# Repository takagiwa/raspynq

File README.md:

# raspynq
Xilinx Virtual Cable Server adapter for Raspberry Pi

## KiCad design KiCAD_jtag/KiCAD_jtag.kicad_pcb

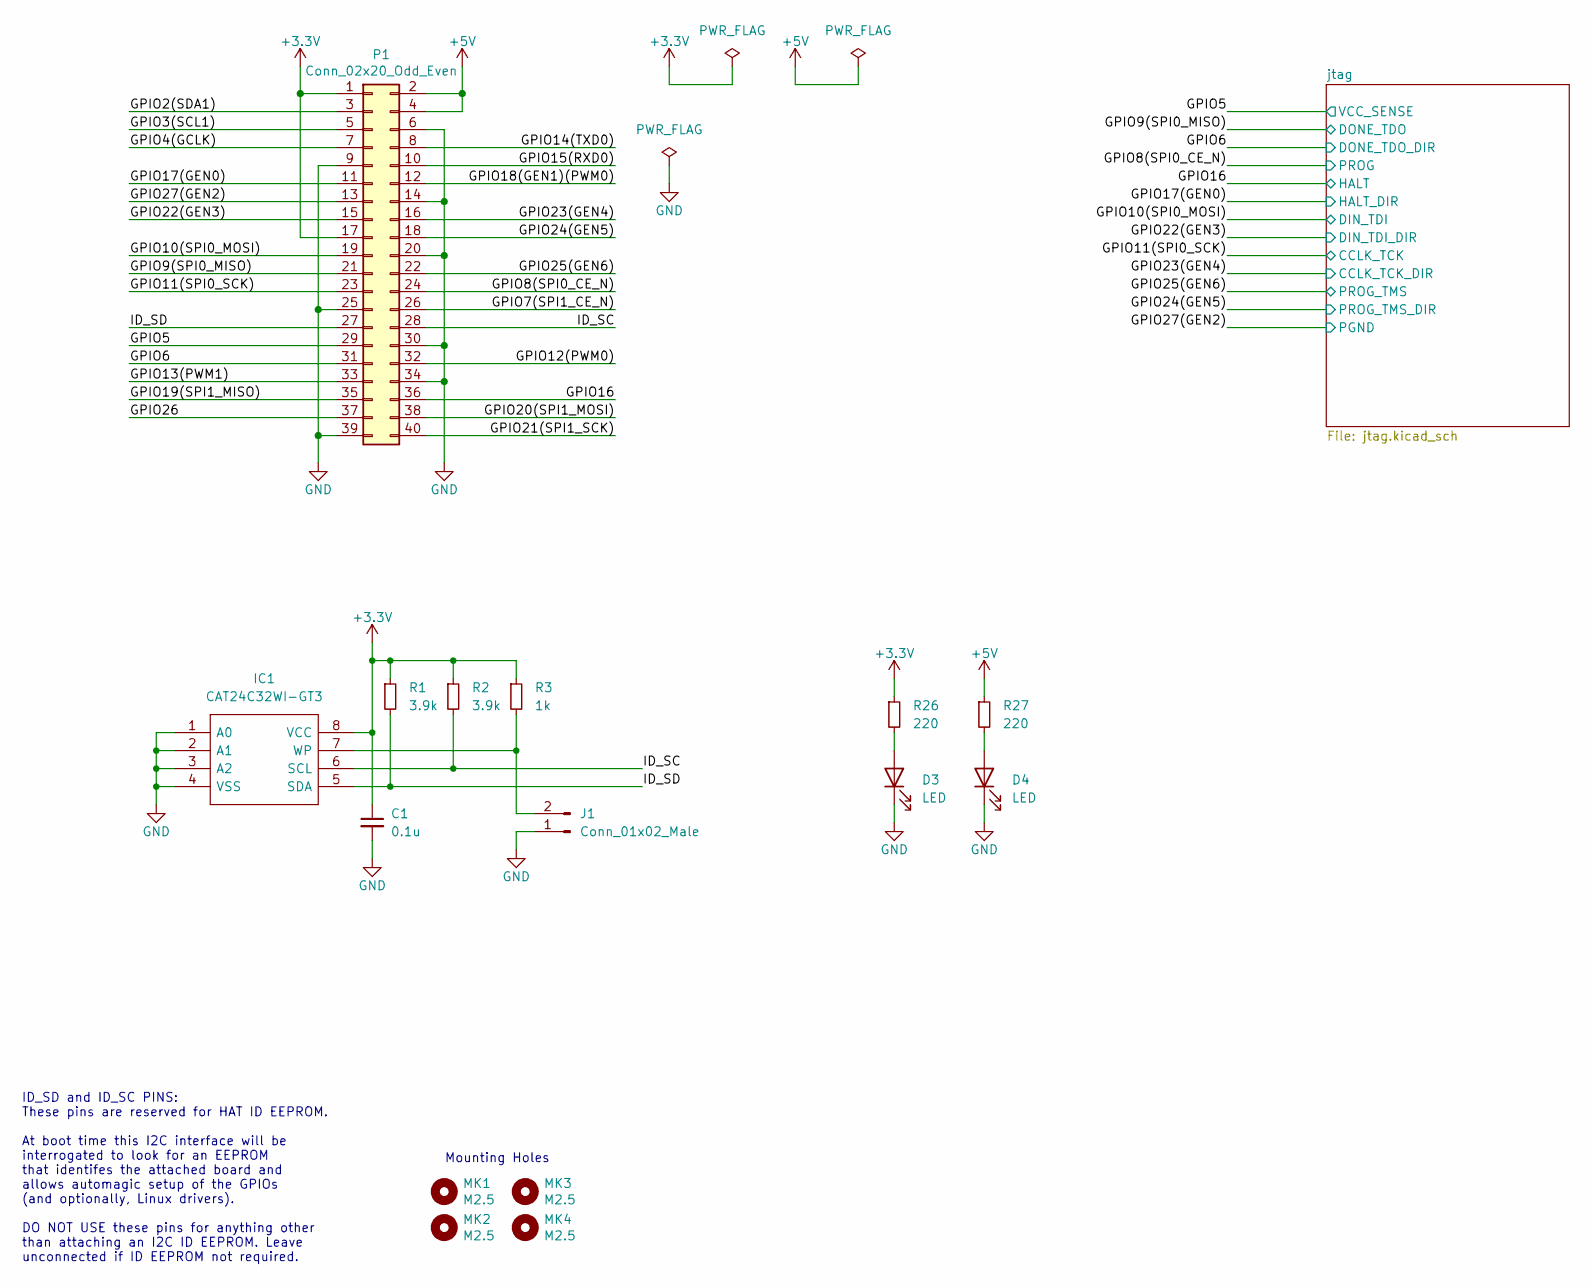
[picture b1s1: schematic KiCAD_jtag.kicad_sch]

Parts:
C1: 0.1u; C_0805_2012Metric_Pad1.18x1.45mm_HandSolder
D3, D4: LED; LED_0805_2012Metric_Pad1.15x1.40mm_HandSolder
IC1: CAT24C32WI-GT3; SOIC127P600X175-8N; Mouser Part Number 698-CAT24C32WI-GT3
J1: Conn_01x02_Male; PinHeader_1x02_P2.54mm_Vertical
MK1, MK2, MK3, MK4: M2.5; MountingHole_2.7mm_M2.5
P1: Conn_02x20_Odd_Even; PinSocket_2x20_P2.54mm_Vertical
R1, R2: 3.9k; R_0805_2012Metric_Pad1.20x1.40mm_HandSolder
R3: 1k; R_0805_2012Metric_Pad1.20x1.40mm_HandSolder
R26, R27: 220; R_0805_2012Metric_Pad1.20x1.40mm_HandSolder

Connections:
+3V3: C1.1, IC1.8 (VCC), P1.1, P1.17, R1.1, R2.1, R3.1, R26.1; also elsewhere on the board
+5V: P1.2, P1.4, R27.1
/GPIO2(SDA1): P1.3
/GPIO3(SCL1): P1.5
/GPIO4(GCLK): P1.7
/GPIO5: P1.29; also elsewhere on the board
/GPIO6: P1.31; also elsewhere on the board
/GPIO7(SPI1_CE_N): P1.26
/GPIO8(SPI0_CE_N): P1.24; also elsewhere on the board
/GPIO9(SPI0_MISO): P1.21; also elsewhere on the board
/GPIO10(SPI0_MOSI): P1.19; also elsewhere on the board
/GPIO11(SPI0_SCK): P1.23; also elsewhere on the board
/GPIO12(PWM0): P1.32
/GPIO13(PWM1): P1.33
/GPIO14(TXD0): P1.8
/GPIO15(RXD0): P1.10
/GPIO16: P1.36; also elsewhere on the board
/GPIO17(GEN0): P1.11; also elsewhere on the board
/GPIO18(GEN1)(PWM0): P1.12
/GPIO19(SPI1_MISO): P1.35
/GPIO20(SPI1_MOSI): P1.38
/GPIO21(SPI1_SCK): P1.40
/GPIO22(GEN3): P1.15; also elsewhere on the board
/GPIO23(GEN4): P1.16; also elsewhere on the board
/GPIO24(GEN5): P1.18; also elsewhere on the board
/GPIO25(GEN6): P1.22; also elsewhere on the board
/GPIO26: P1.37
/GPIO27(GEN2): P1.13; also elsewhere on the board
/ID_SC: IC1.6 (SCL), P1.28, R2.2
/ID_SD: IC1.5 (SDA), P1.27, R1.2
GND: C1.2, D3.1 (K), D4.1 (K), IC1.1 (A0), IC1.2 (A1), IC1.3 (A2), IC1.4 (VSS), J1.1, P1.6, P1.9, P1.14, P1.20, P1.25, P1.30, P1.34, P1.39; also elsewhere on the board
unnamed: D3.2 (A), R26.2
unnamed: D4.2 (A), R27.2
unnamed: IC1.7 (WP), J1.2, R3.2

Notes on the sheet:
ID_SD and ID_SC PINS: These pins are reserved for HAT ID EEPROM. At boot time this I2C interface will be interrogated to look for an EEPROM that identifes the attached board and allows automagic setup of the GPIOs (and optionally, Linux drivers). DO NOT USE these pins for anything other than attach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
Mounting Holes

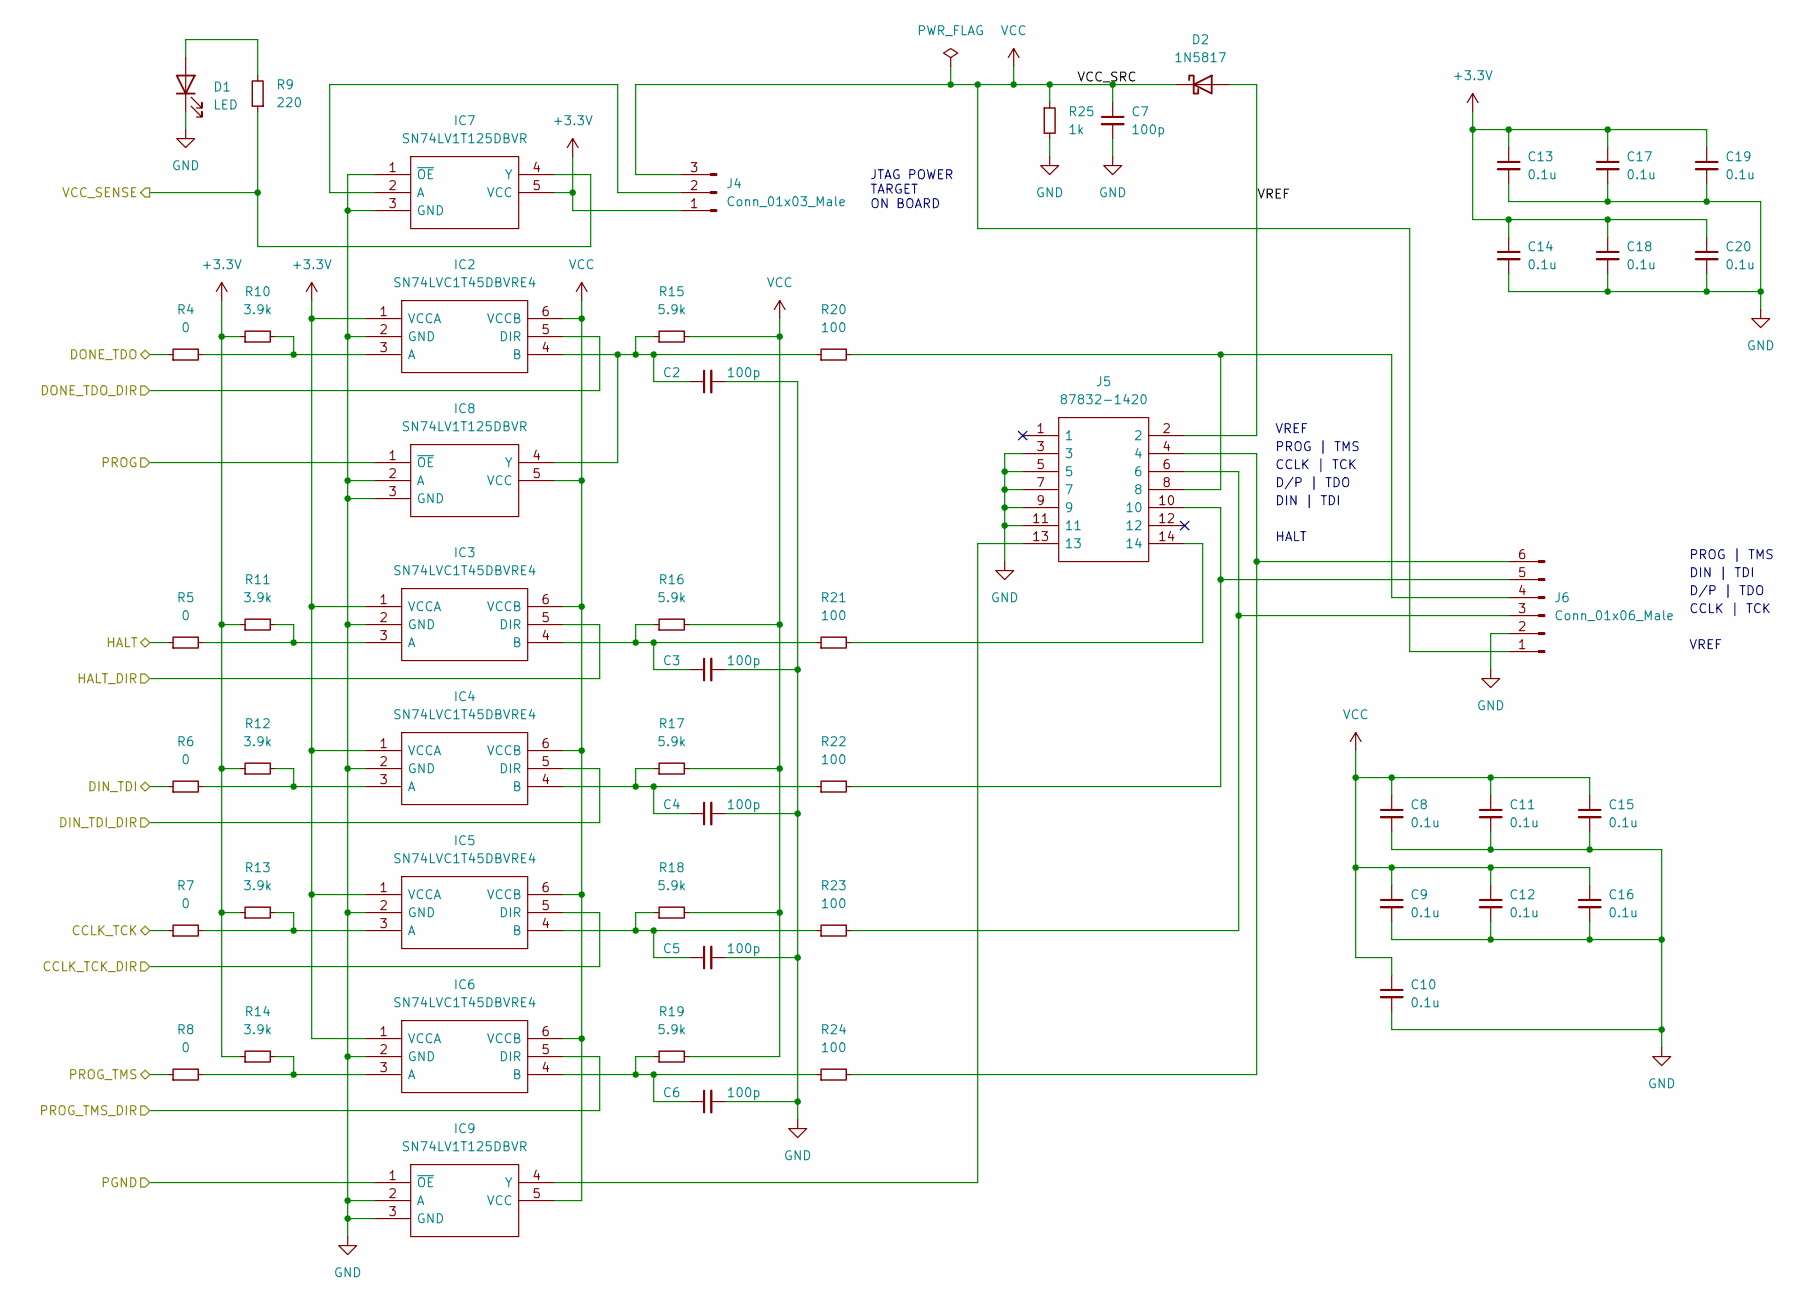
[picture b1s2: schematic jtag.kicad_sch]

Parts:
C2, C3, C4, C5, C6, C7: 100p; C_0805_2012Metric_Pad1.18x1.45mm_HandSolder
C8, C9, C10, C11, C12, C13, C14, C15, C16, C17, C18, C19, C20: 0.1u; C_0805_2012Metric_Pad1.18x1.45mm_HandSolder
D1: LED; LED_0805_2012Metric_Pad1.15x1.40mm_HandSolder
D2: 1N5817; D_DO-41_SOD81_P10.16mm_Horizontal
IC2, IC3, IC4, IC5, IC6: SN74LVC1T45DBVRE4; SOT95P280X145-6N; Mouser Part Number 595-74LVC1T45DBVRE4
IC7, IC8, IC9: SN74LV1T125DBVR; SOT95P280X145-5N; Mouser Part Number 595-SN74LV1T125DBVR
J4: Conn_01x03_Male; PinHeader_1x03_P2.54mm_Vertical
J5: 87832-1420; Mouser Part Number 538-87832-1420
J6: Conn_01x06_Male; PinHeader_1x06_P2.54mm_Vertical
R4, R5, R6, R7, R8: 0; R_0805_2012Metric_Pad1.20x1.40mm_HandSolder
R9: 220; R_0805_2012Metric_Pad1.20x1.40mm_HandSolder
R10, R11, R12, R13, R14: 3.9k; R_0805_2012Metric_Pad1.20x1.40mm_HandSolder
R15, R16, R17, R18, R19: 5.9k; R_0805_2012Metric_Pad1.20x1.40mm_HandSolder
R20, R21, R22, R23, R24: 100; R_0805_2012Metric_Pad1.20x1.40mm_HandSolder
R25: 1k; R_0805_2012Metric_Pad1.20x1.40mm_HandSolder

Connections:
+3V3: C13.1, C14.1, C17.1, C18.1, C19.1, C20.1, IC2.1 (VCCA), IC3.1 (VCCA), IC4.1 (VCCA), IC5.1 (VCCA), IC6.1 (VCCA), IC7.5 (VCC), J4.1, R10.1, R11.1, R12.1, R13.1, R14.1; also elsewhere on the board
/GPIO5: IC7.4 (Y), R9.1; also elsewhere on the board
/GPIO6: IC2.5 (DIR); also elsewhere on the board
/GPIO8(SPI0_CE_N): IC8.1 (~OE); also elsewhere on the board
/GPIO9(SPI0_MISO): R4.1; also elsewhere on the board
/GPIO10(SPI0_MOSI): R6.1; also elsewhere on the board
/GPIO11(SPI0_SCK): R7.1; also elsewhere on the board
/GPIO16: R5.1; also elsewhere on the board
/GPIO17(GEN0): IC3.5 (DIR); also elsewhere on the board
/GPIO22(GEN3): IC4.5 (DIR); also elsewhere on the board
/GPIO23(GEN4): IC5.5 (DIR); also elsewhere on the board
/GPIO24(GEN5): IC6.5 (DIR); also elsewhere on the board
/GPIO25(GEN6): R8.1; also elsewhere on the board
/GPIO27(GEN2): IC9.1 (~OE); also elsewhere on the board
/jtag/VREF: D2.2 (A), J5.2
GND: C2.2, C3.2, C4.2, C5.2, C6.2, C7.2, C8.2, C9.2, C10.2, C11.2, C12.2, C13.2, C14.2, C15.2, C16.2, C17.2, C18.2, C19.2, C20.2, D1.1 (K), IC2.2 (GND), IC3.2 (GND), IC4.2 (GND), IC5.2 (GND), IC6.2 (GND), IC7.1 (~OE), IC7.3 (GND), IC8.2 (A), IC8.3 (GND), IC9.2 (A), IC9.3 (GND), J5.3, J5.5, J5.7, J5.9, J5.11, J6.2, R25.2; also elsewhere on the board
unnamed: C2.1, IC2.4 (B), IC8.4 (Y), R15.1, R20.1
unnamed: C3.1, IC3.4 (B), R16.1, R21.1
unnamed: C4.1, IC4.4 (B), R17.1, R22.1
unnamed: C5.1, IC5.4 (B), R18.1, R23.1
unnamed: C6.1, IC6.4 (B), R19.1, R24.1
unnamed: D1.2 (A), R9.2
unnamed: IC2.3 (A), R4.2, R10.2
unnamed: IC3.3 (A), R5.2, R11.2
unnamed: IC4.3 (A), R6.2, R12.2
unnamed: IC5.3 (A), R7.2, R13.2
unnamed: IC6.3 (A), R8.2, R14.2
unnamed: IC7.2 (A), J4.2
unnamed: IC9.4 (Y), J5.13
unnamed: J5.4, J6.6, R24.2
unnamed: J5.6, J6.3, R23.2
unnamed: J5.8, J6.4, R20.2
unnamed: J5.10, J6.5, R22.2
unnamed: J5.14, R21.2
VCC: C7.1, C8.1, C9.1, C10.1, C11.1, C12.1, C15.1, C16.1, D2.1 (K), IC2.6 (VCCB), IC3.6 (VCCB), IC4.6 (VCCB), IC5.6 (VCCB), IC6.6 (VCCB), IC8.5 (VCC), IC9.5 (VCC), J4.3, J6.1, R15.2, R16.2, R17.2, R18.2, R19.2, R25.1

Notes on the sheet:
CCLK | TCK
VREF
PROG | TMS
D/P | TDO
HALT
DIN | TDI
JTAG POWER TARGET ON BOARD

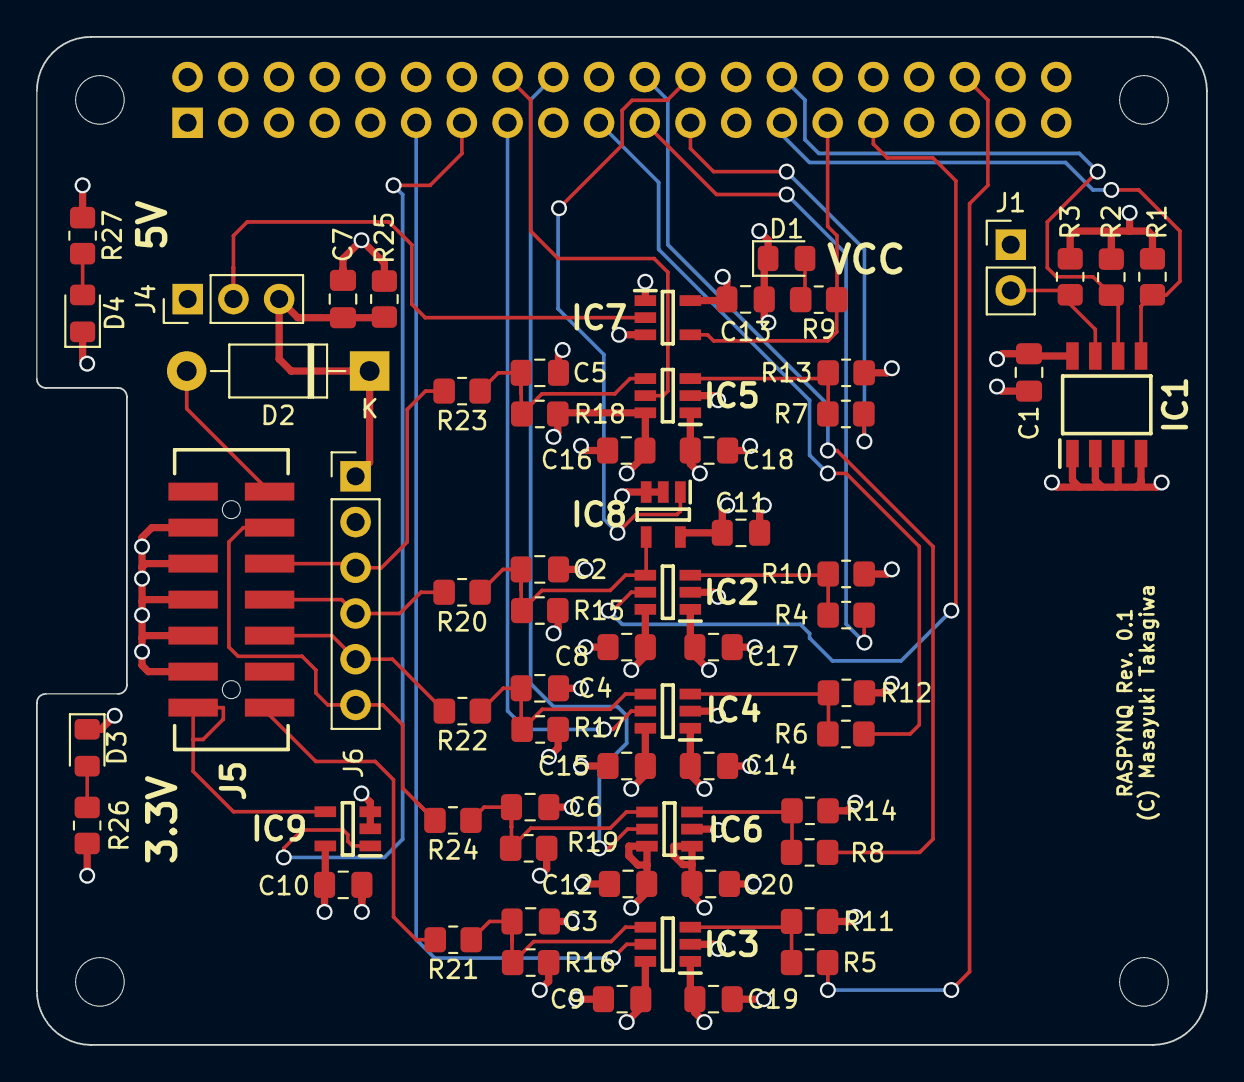
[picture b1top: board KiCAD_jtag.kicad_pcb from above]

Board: 4 copper layers, 65.0 x 56.0 mm, 69 parts (1 on the bottom side), 41 nets.

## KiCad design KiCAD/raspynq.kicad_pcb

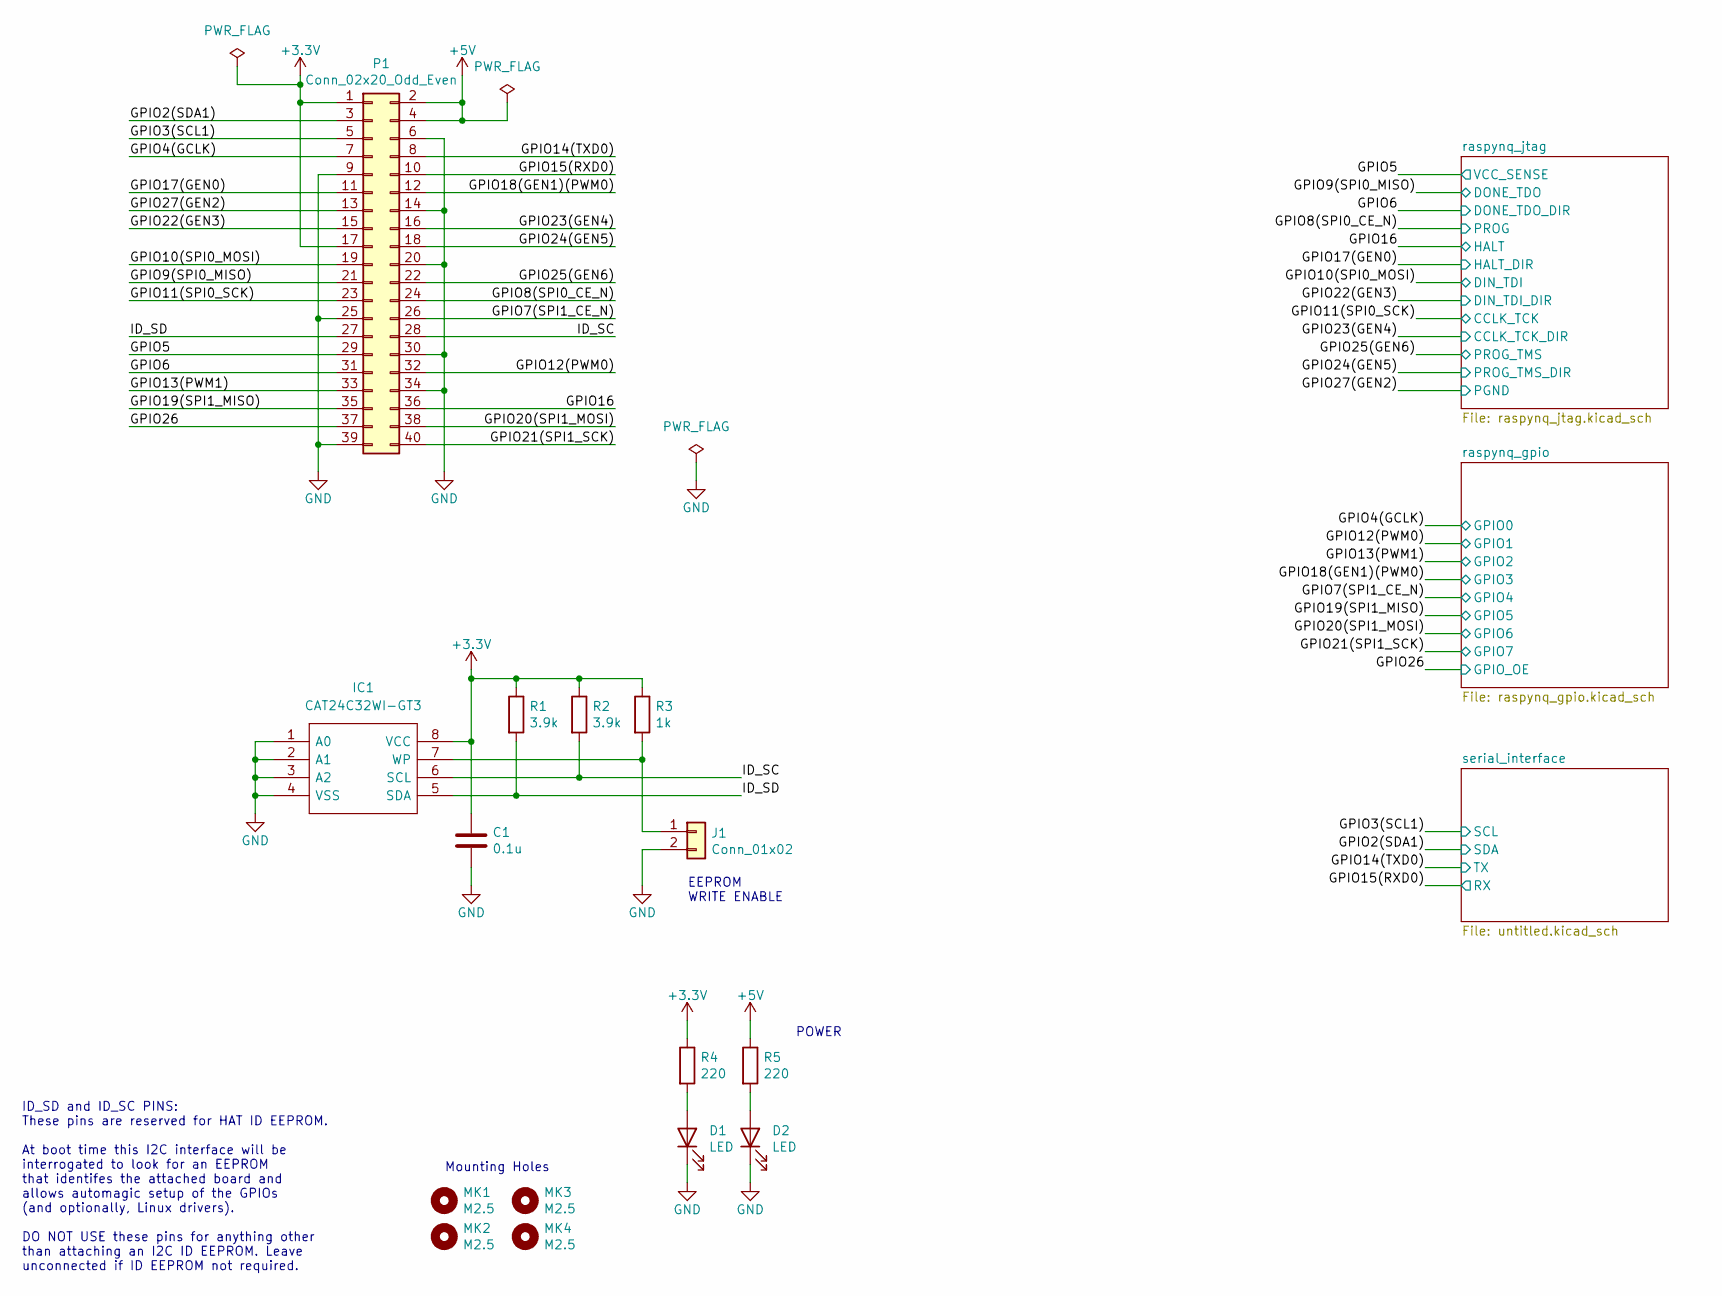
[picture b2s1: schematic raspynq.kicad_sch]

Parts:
C1: 0.1u; C_0805_2012Metric_Pad1.18x1.45mm_HandSolder
D1, D2: LED; LED_0805_2012Metric_Pad1.15x1.40mm_HandSolder
IC1: CAT24C32WI-GT3; SOIC127P600X175-8N; Mouser Part Number 698-CAT24C32WI-GT3
J1: Conn_01x02; PinHeader_1x02_P2.54mm_Vertical
MK1, MK2, MK3, MK4: M2.5; MountingHole_2.7mm_M2.5
P1: Conn_02x20_Odd_Even; PinSocket_2x20_P2.54mm_Vertical
R1, R2: 3.9k; R_0805_2012Metric_Pad1.20x1.40mm_HandSolder
R3: 1k; R_0805_2012Metric_Pad1.20x1.40mm_HandSolder
R4, R5: 220; R_0805_2012Metric_Pad1.20x1.40mm_HandSolder

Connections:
+3V3: C1.1, IC1.8 (VCC), P1.1, P1.17, R1.1, R2.1, R3.1, R4.1; also elsewhere on the board
+5V: P1.2, P1.4, R5.1; also elsewhere on the board
/GPIO2(SDA1): P1.3; also elsewhere on the board
/GPIO3(SCL1): P1.5; also elsewhere on the board
/GPIO4(GCLK): P1.7; also elsewhere on the board
/GPIO5: P1.29; also elsewhere on the board
/GPIO6: P1.31; also elsewhere on the board
/GPIO7(SPI1_CE_N): P1.26; also elsewhere on the board
/GPIO8(SPI0_CE_N): P1.24; also elsewhere on the board
/GPIO9(SPI0_MISO): P1.21; also elsewhere on the board
/GPIO10(SPI0_MOSI): P1.19; also elsewhere on the board
/GPIO11(SPI0_SCK): P1.23; also elsewhere on the board
/GPIO12(PWM0): P1.32; also elsewhere on the board
/GPIO13(PWM1): P1.33; also elsewhere on the board
/GPIO14(TXD0): P1.8; also elsewhere on the board
/GPIO15(RXD0): P1.10; also elsewhere on the board
/GPIO16: P1.36; also elsewhere on the board
/GPIO17(GEN0): P1.11; also elsewhere on the board
/GPIO18(GEN1)(PWM0): P1.12; also elsewhere on the board
/GPIO19(SPI1_MISO): P1.35; also elsewhere on the board
/GPIO20(SPI1_MOSI): P1.38; also elsewhere on the board
/GPIO21(SPI1_SCK): P1.40; also elsewhere on the board
/GPIO22(GEN3): P1.15; also elsewhere on the board
/GPIO23(GEN4): P1.16; also elsewhere on the board
/GPIO24(GEN5): P1.18; also elsewhere on the board
/GPIO25(GEN6): P1.22; also elsewhere on the board
/GPIO26: P1.37; also elsewhere on the board
/GPIO27(GEN2): P1.13; also elsewhere on the board
/ID_SC: IC1.6 (SCL), P1.28, R2.2
/ID_SD: IC1.5 (SDA), P1.27, R1.2
GND: C1.2, D1.1 (K), D2.1 (K), IC1.1 (A0), IC1.2 (A1), IC1.3 (A2), IC1.4 (VSS), J1.2, P1.6, P1.9, P1.14, P1.20, P1.25, P1.30, P1.34, P1.39; also elsewhere on the board
unnamed: D1.2 (A), R4.2
unnamed: D2.2 (A), R5.2
unnamed: IC1.7 (WP), J1.1, R3.2

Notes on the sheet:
Mounting Holes
EEPROM WRITE ENABLE
ID_SD and ID_SC PINS: These pins are reserved for HAT ID EEPROM. At boot time this I2C interface will be interrogated to look for an EEPROM that identifes the attached board and allows automagic setup of the GPIOs (and optionally, Linux drivers). DO NOT USE these pins for anything other than attach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
POWER

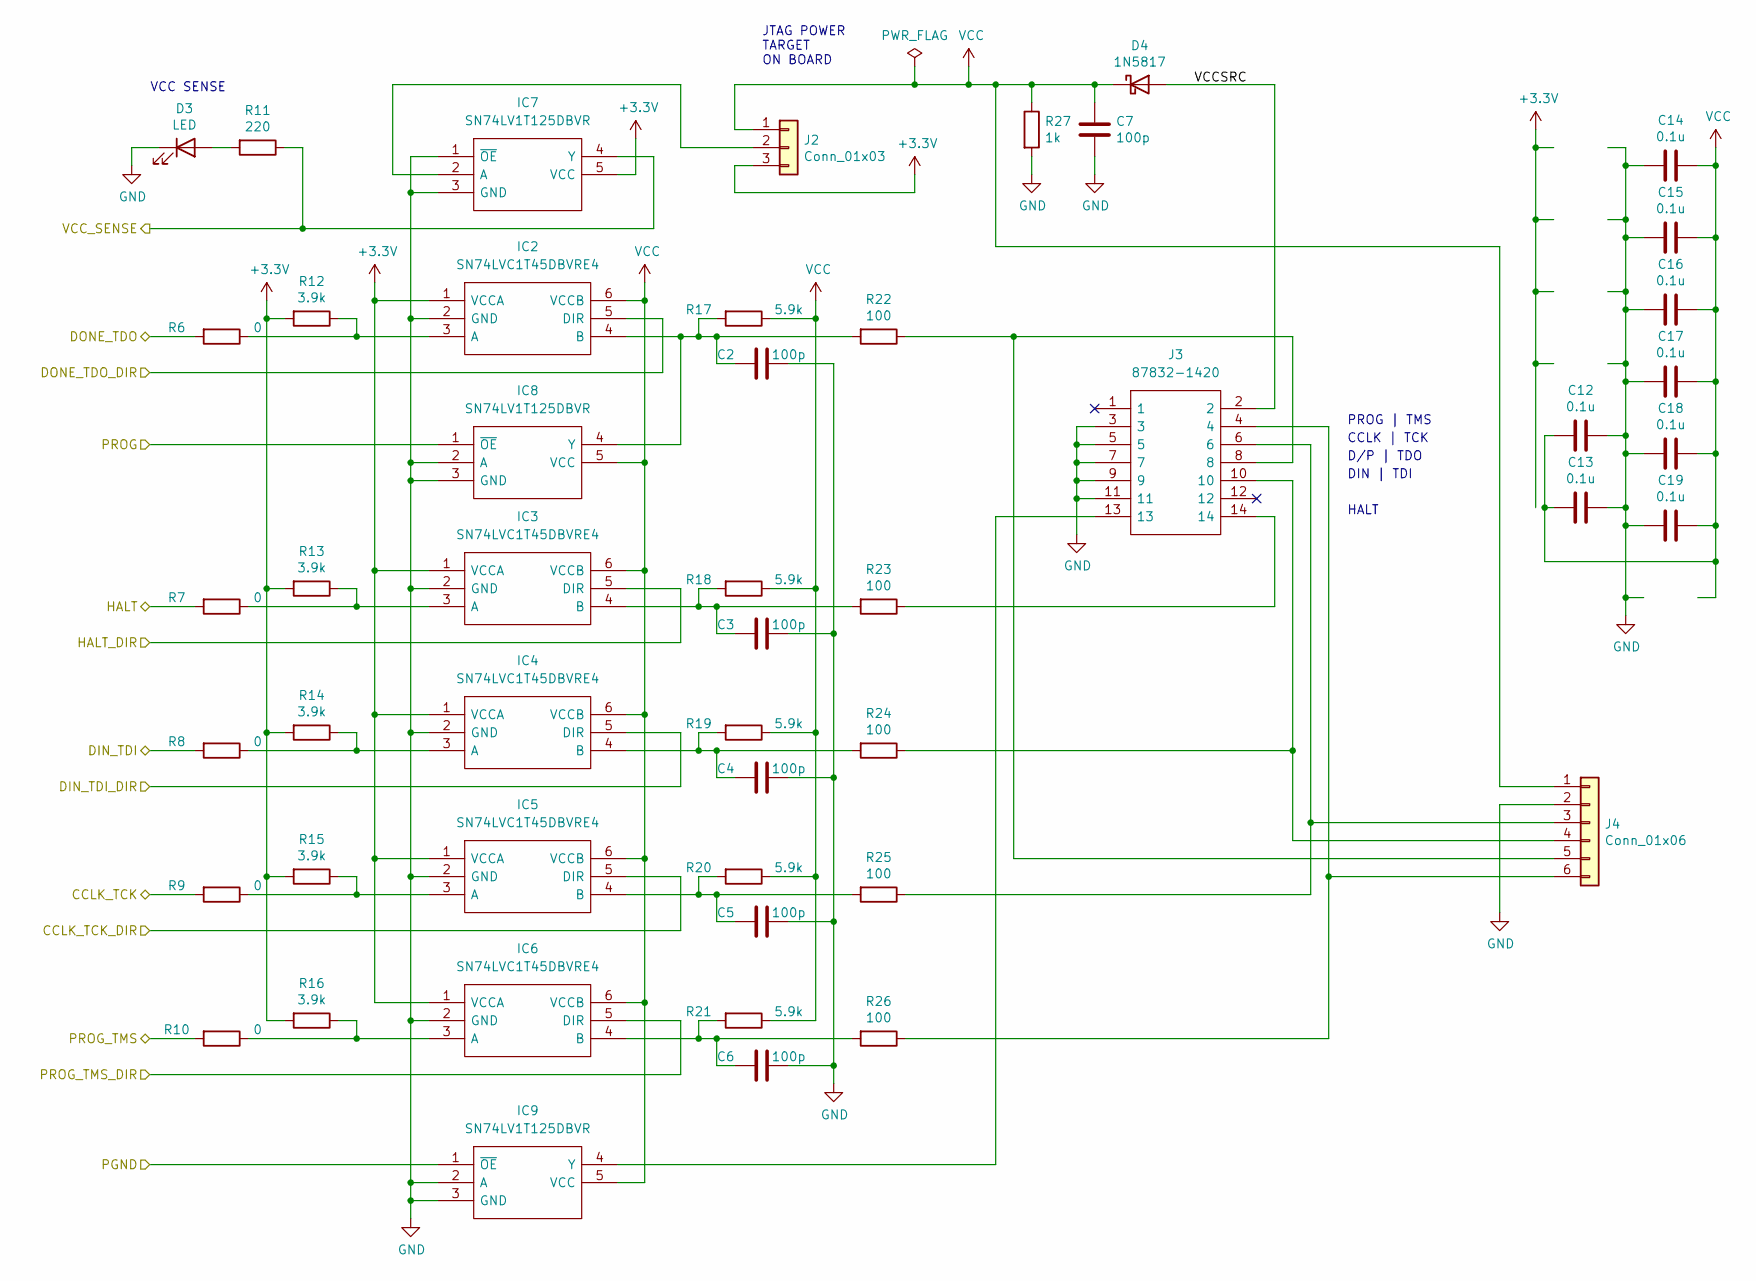
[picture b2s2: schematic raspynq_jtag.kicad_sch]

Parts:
C2, C3, C4, C5, C6, C7: 100p; C_0805_2012Metric_Pad1.18x1.45mm_HandSolder
C12, C13, C14, C15, C16, C17, C18, C19: 0.1u; C_0805_2012Metric_Pad1.18x1.45mm_HandSolder
D3: LED; LED_0805_2012Metric_Pad1.15x1.40mm_HandSolder
D4: 1N5817; D_DO-41_SOD81_P10.16mm_Horizontal
IC2, IC3, IC4, IC5, IC6: SN74LVC1T45DBVRE4; SOT95P280X145-6N; Mouser Part Number 595-74LVC1T45DBVRE4
IC7, IC8, IC9: SN74LV1T125DBVR; SOT95P280X145-5N; Mouser Part Number 595-SN74LV1T125DBVR
J2: Conn_01x03; PinHeader_1x03_P2.54mm_Vertical
J3: 87832-1420; Mouser Part Number 538-87832-1420
J4: Conn_01x06; PinHeader_1x06_P2.54mm_Vertical
R6, R7, R8, R9, R10: 0; R_0805_2012Metric_Pad1.20x1.40mm_HandSolder
R11: 220; R_0805_2012Metric_Pad1.20x1.40mm_HandSolder
R12, R13, R14, R15, R16: 3.9k; R_0805_2012Metric_Pad1.20x1.40mm_HandSolder
R17, R18, R19, R20, R21: 5.9k; R_0805_2012Metric_Pad1.20x1.40mm_HandSolder
R22, R23, R24, R25, R26: 100; R_0805_2012Metric_Pad1.20x1.40mm_HandSolder
R27: 1k; R_0805_2012Metric_Pad1.20x1.40mm_HandSolder

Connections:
+3V3: IC2.1 (VCCA), IC3.1 (VCCA), IC4.1 (VCCA), IC5.1 (VCCA), IC6.1 (VCCA), IC7.5 (VCC), J2.3, R12.2, R13.2, R14.2, R15.2, R16.2; also elsewhere on the board
/GPIO5: IC7.4 (Y), R11.1; also elsewhere on the board
/GPIO6: IC2.5 (DIR); also elsewhere on the board
/GPIO8(SPI0_CE_N): IC8.1 (~OE); also elsewhere on the board
/GPIO9(SPI0_MISO): R6.2; also elsewhere on the board
/GPIO10(SPI0_MOSI): R8.2; also elsewhere on the board
/GPIO11(SPI0_SCK): R9.2; also elsewhere on the board
/GPIO16: R7.2; also elsewhere on the board
/GPIO17(GEN0): IC3.5 (DIR); also elsewhere on the board
/GPIO22(GEN3): IC4.5 (DIR); also elsewhere on the board
/GPIO23(GEN4): IC5.5 (DIR); also elsewhere on the board
/GPIO24(GEN5): IC6.5 (DIR); also elsewhere on the board
/GPIO25(GEN6): R10.2; also elsewhere on the board
/GPIO27(GEN2): IC9.1 (~OE); also elsewhere on the board
/raspynq_jtag/VCCSRC: D4.2 (A), J3.2
GND: C2.1, C3.1, C4.1, C5.1, C6.1, C7.2, C12.1, C13.1, C14.2, C15.2, C16.2, C17.2, C18.2, C19.2, D3.1 (K), IC2.2 (GND), IC3.2 (GND), IC4.2 (GND), IC5.2 (GND), IC6.2 (GND), IC7.1 (~OE), IC7.3 (GND), IC8.2 (A), IC8.3 (GND), IC9.2 (A), IC9.3 (GND), J3.3, J3.5, J3.7, J3.9, J3.11, J4.2, R27.2; also elsewhere on the board
unnamed: C2.2, IC2.4 (B), IC8.4 (Y), R17.2, R22.2
unnamed: C3.2, IC3.4 (B), R18.2, R23.2
unnamed: C4.2, IC4.4 (B), R19.2, R24.2
unnamed: C5.2, IC5.4 (B), R20.2, R25.2
unnamed: C6.2, IC6.4 (B), R21.2, R26.2
unnamed: D3.2 (A), R11.2
unnamed: IC2.3 (A), R6.1, R12.1
unnamed: IC3.3 (A), R7.1, R13.1
unnamed: IC4.3 (A), R8.1, R14.1
unnamed: IC5.3 (A), R9.1, R15.1
unnamed: IC6.3 (A), R10.1, R16.1
unnamed: IC7.2 (A), J2.2
unnamed: IC9.4 (Y), J3.13
unnamed: J3.4, J4.6, R26.1
unnamed: J3.6, J4.3, R25.1
unnamed: J3.8, J4.5, R22.1
unnamed: J3.10, J4.4, R24.1
unnamed: J3.14, R23.1
VCC: C7.1, C12.2, C13.2, C14.1, C15.1, C16.1, C17.1, C18.1, C19.1, D4.1 (K), IC2.6 (VCCB), IC3.6 (VCCB), IC4.6 (VCCB), IC5.6 (VCCB), IC6.6 (VCCB), IC8.5 (VCC), IC9.5 (VCC), J2.1, J4.1, R17.1, R18.1, R19.1, R20.1, R21.1, R27.1

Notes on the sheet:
DIN | TDI
VCC SENSE
D/P | TDO
JTAG POWER TARGET ON BOARD
PROG | TMS
CCLK | TCK
HALT

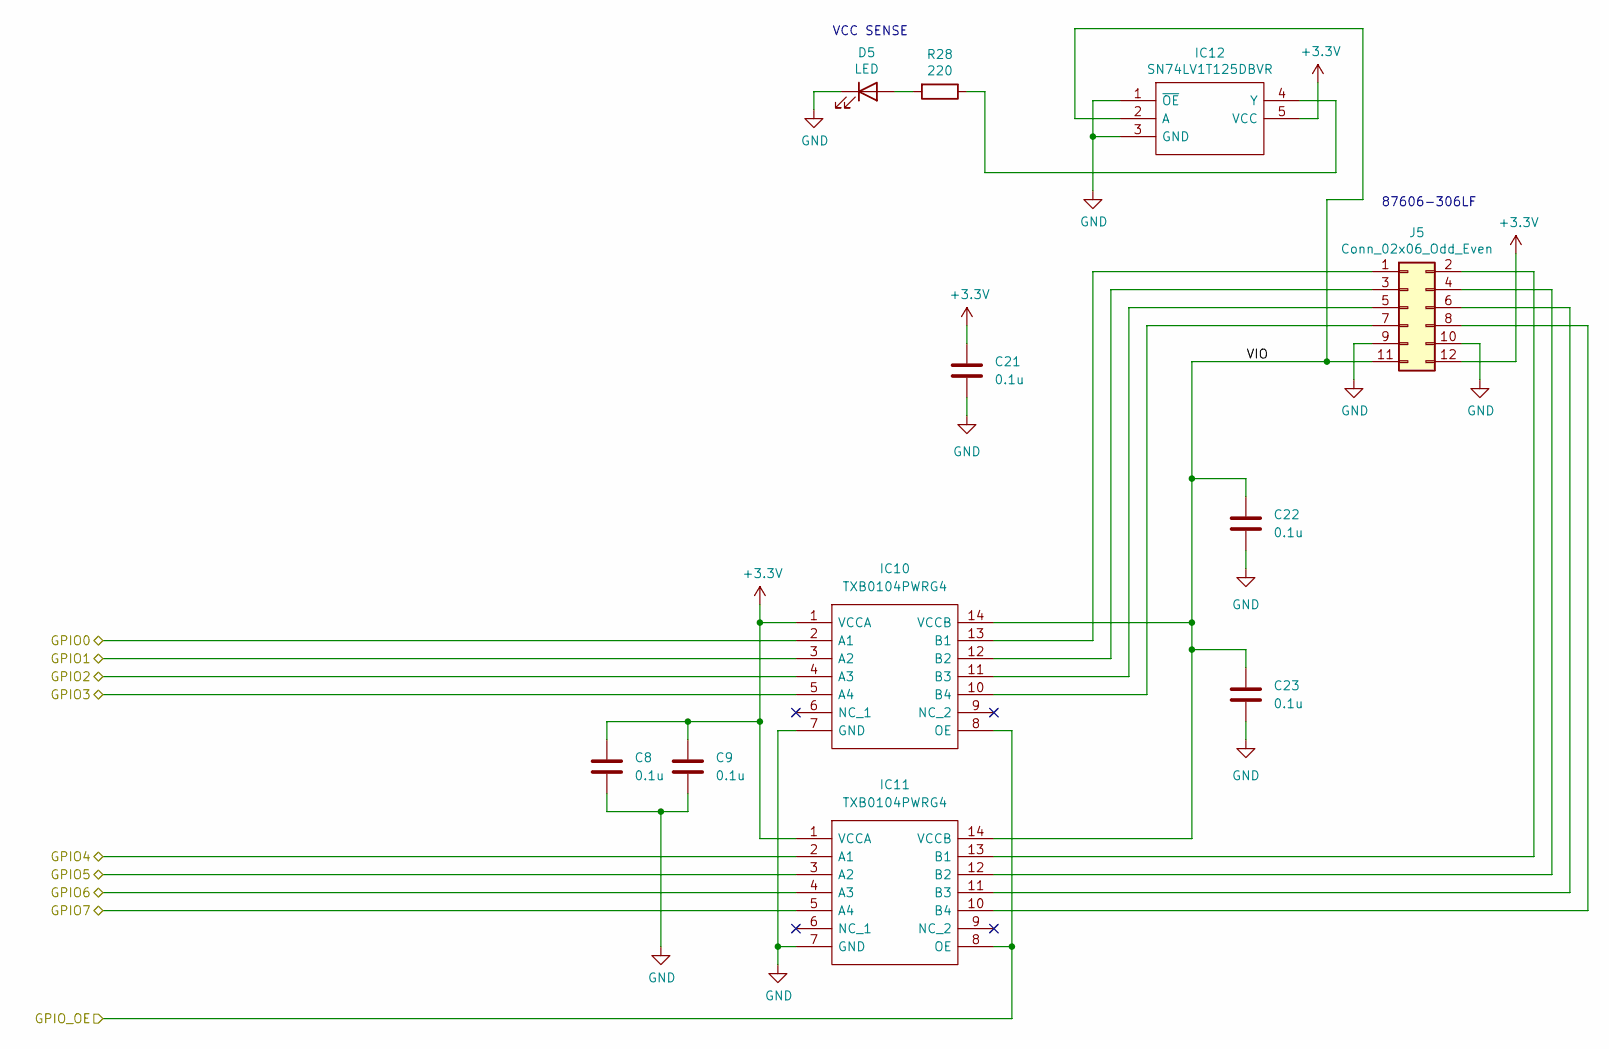
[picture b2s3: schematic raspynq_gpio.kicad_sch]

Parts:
C8, C9, C21, C22, C23: 0.1u; C_0805_2012Metric_Pad1.18x1.45mm_HandSolder
D5: LED; LED_0805_2012Metric_Pad1.15x1.40mm_HandSolder
IC10, IC11: TXB0104PWRG4; SOP65P640X120-14N; Mouser Part Number 595-TXB0104PWRG4
IC12: SN74LV1T125DBVR; SOT95P280X145-5N; Mouser Part Number 595-SN74LV1T125DBVR
J5: Conn_02x06_Odd_Even; PinHeader_2x06_P2.54mm_Vertical
R28: 220; R_0805_2012Metric_Pad1.20x1.40mm_HandSolder

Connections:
+3V3: C8.1, C9.1, C21.1, IC10.1 (VCCA), IC11.1 (VCCA), IC12.5 (VCC), J5.12; also elsewhere on the board
/GPIO4(GCLK): IC10.2 (A1); also elsewhere on the board
/GPIO7(SPI1_CE_N): IC11.2 (A1); also elsewhere on the board
/GPIO12(PWM0): IC10.3 (A2); also elsewhere on the board
/GPIO13(PWM1): IC10.4 (A3); also elsewhere on the board
/GPIO18(GEN1)(PWM0): IC10.5 (A4); also elsewhere on the board
/GPIO19(SPI1_MISO): IC11.3 (A2); also elsewhere on the board
/GPIO20(SPI1_MOSI): IC11.4 (A3); also elsewhere on the board
/GPIO21(SPI1_SCK): IC11.5 (A4); also elsewhere on the board
/GPIO26: IC10.8 (OE), IC11.8 (OE); also elsewhere on the board
/raspynq_gpio/VIO: C22.1, C23.1, IC10.14 (VCCB), IC11.14 (VCCB), IC12.2 (A), J5.11
GND: C8.2, C9.2, C21.2, C22.2, C23.2, D5.1 (K), IC10.7 (GND), IC11.7 (GND), IC12.1 (~OE), IC12.3 (GND), J5.9, J5.10; also elsewhere on the board
unnamed: D5.2 (A), R28.2
unnamed: IC10.10 (B4), J5.7
unnamed: IC10.11 (B3), J5.5
unnamed: IC10.12 (B2), J5.3
unnamed: IC10.13 (B1), J5.1
unnamed: IC11.10 (B4), J5.8
unnamed: IC11.11 (B3), J5.6
unnamed: IC11.12 (B2), J5.4
unnamed: IC11.13 (B1), J5.2
unnamed: IC12.4 (Y), R28.1

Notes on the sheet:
VCC SENSE
87606-306LF

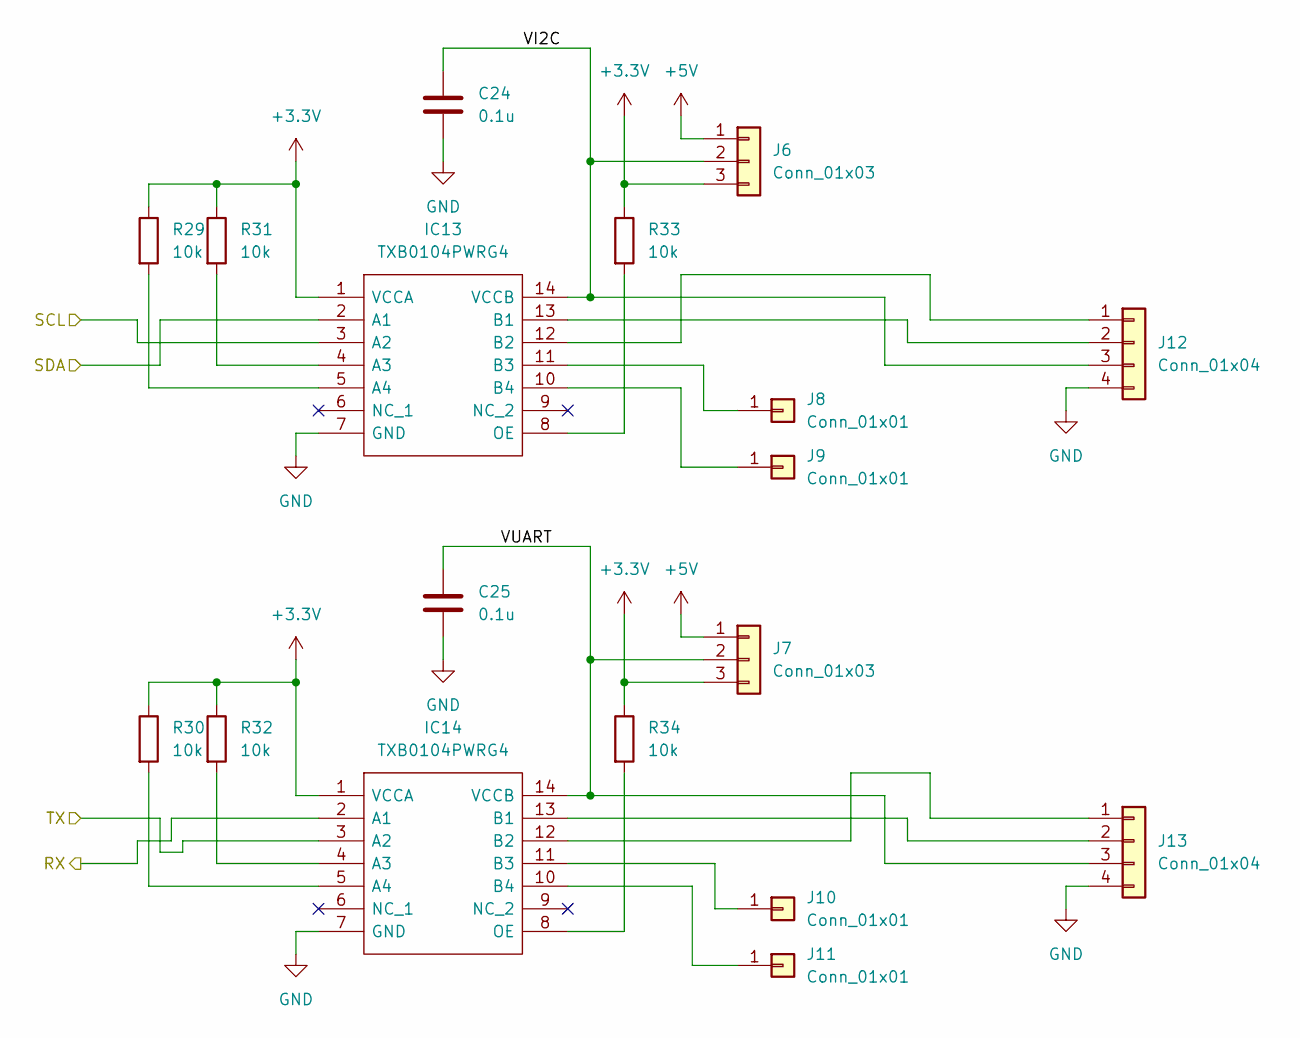
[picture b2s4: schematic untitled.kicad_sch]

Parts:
C24, C25: 0.1u; C_0805_2012Metric_Pad1.18x1.45mm_HandSolder
IC13, IC14: TXB0104PWRG4; SOP65P640X120-14N; Mouser Part Number 595-TXB0104PWRG4
J6, J7: Conn_01x03; PinHeader_1x03_P2.54mm_Vertical
J8, J9, J10, J11: Conn_01x01; TestPoint_Pad_D1.0mm
J12, J13: Conn_01x04; PinHeader_1x04_P2.00mm_Vertical
R29, R30, R31, R32, R33, R34: 10k; R_0805_2012Metric_Pad1.20x1.40mm_HandSolder

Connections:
+3V3: IC13.1 (VCCA), IC14.1 (VCCA), J6.3, J7.3, R29.1, R30.1, R31.1, R32.1, R33.1, R34.1; also elsewhere on the board
+5V: J6.1, J7.1; also elsewhere on the board
/GPIO2(SDA1): IC13.2 (A1); also elsewhere on the board
/GPIO3(SCL1): IC13.3 (A2); also elsewhere on the board
/GPIO14(TXD0): IC14.3 (A2); also elsewhere on the board
/GPIO15(RXD0): IC14.2 (A1); also elsewhere on the board
/serial_interface/VI2C: C24.1, IC13.14 (VCCB), J6.2, J12.3
/serial_interface/VUART: C25.1, IC14.14 (VCCB), J7.2, J13.3
GND: C24.2, C25.2, IC13.7 (GND), IC14.7 (GND), J12.4, J13.4; also elsewhere on the board
unnamed: IC13.4 (A3), R31.2
unnamed: IC13.5 (A4), R29.2
unnamed: IC13.8 (OE), R33.2
unnamed: IC13.10 (B4), J9.1
unnamed: IC13.11 (B3), J8.1
unnamed: IC13.12 (B2), J12.1
unnamed: IC13.13 (B1), J12.2
unnamed: IC14.4 (A3), R32.2
unnamed: IC14.5 (A4), R30.2
unnamed: IC14.8 (OE), R34.2
unnamed: IC14.10 (B4), J11.1
unnamed: IC14.11 (B3), J10.1
unnamed: IC14.12 (B2), J13.1
unnamed: IC14.13 (B1), J13.2
